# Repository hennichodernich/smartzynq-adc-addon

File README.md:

# smartzynq-adc-addon
KiCad files for the SmartZynq ADC addon board

*Make sure to reconfigure VCCIO on the SmartZynq to 2.5V!*

Licensed under CERN-OHL-W v2

## Hardware build

This board is supposed to be mounted on a HelloFPGA Smart Zynq SL FPGA board such as the one that can be purchased [here](https://aliexpress.com/item/1005006384235496.html).

It can be nicely mounted in an enclosure such as [this one](https://aliexpress.com/item/1005007125132369.html):

## Receive performance

The receive performance of the [sdr_receiver_ft8_122_88 project](https://github.com/hennichodernich/hellofpga-smartzynq-notes/tree/main/projects/sdr_receiver_ft8_122_88) is really good (on 22m EFHW):

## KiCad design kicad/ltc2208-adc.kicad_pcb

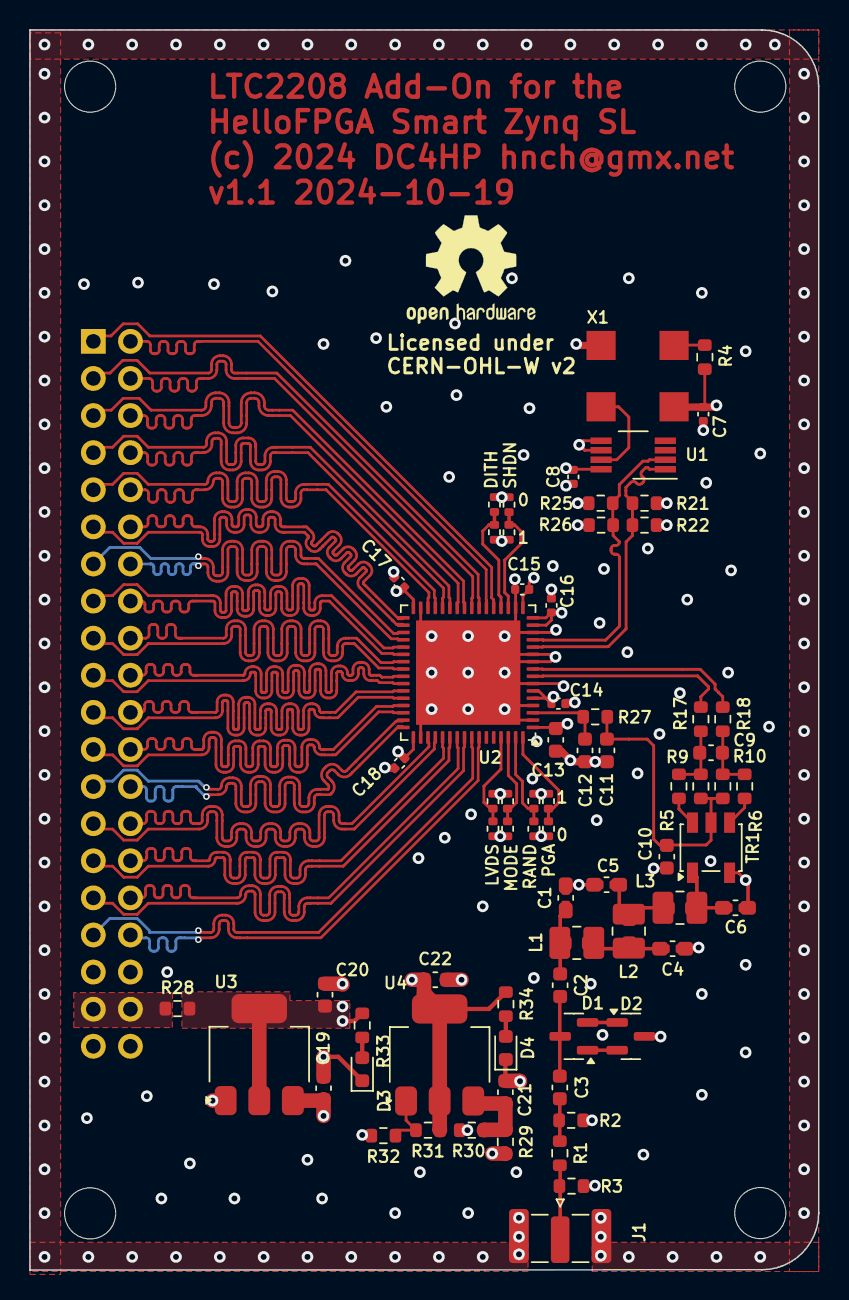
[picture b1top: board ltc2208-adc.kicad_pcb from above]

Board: 4 copper layers, 54.0 x 84.9 mm, 75 parts (1 on the bottom side), 70 nets.

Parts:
C1, C4, C5, C6: C; C_0603_0402_HandSolder_Combo
C2, C3: 1u; C_0603_1608Metric
C7, C8, C14, C15, C16, C17, C18: 100n; C_0402_1005Metric
C9: 4.7p; C_0603_1608Metric
C10, C11: 10n; C_0603_1608Metric
C12, C13, C19, C20, C21, C22: 2.2u; C_0603_1608Metric
D1, D2: BAV99; SOT-23
D3, D4: LED; LED_0603_1608Metric
H1, H2, H3, H4: MountingHole; MountingHole_3.5mm
J1: Conn_Coaxial; SMA_Samtec_SMA-J-P-H-ST-EM1_EdgeMount
J2: Conn_02x20_Odd_Even; PinSocket_2x20_P2.54mm_Vertical
L1, L2, L3: L; L_1008_0805_0603_HandSolder_Combo
R1: 5.1; R_0603_1608Metric
R2, R3: 1k; R_0603_1608Metric
R4: 4.7k; R_0603_1608Metric
R5, R6, R17, R18: 10; R_0603_1608Metric
R7, R8, R11, R12, R13, R14, R15, R16, R19, R20, R23, R24: 4.7k; R_0402_1005Metric
R9, R10: 33.2; R_0603_1608Metric
R21, R25: 130; R_0603_1608Metric
R22, R26: 83; R_0603_1608Metric
R27: 100; R_0603_1608Metric
R28, R29, R30: 0; R_0603_1608Metric
R31, R32: R; R_0603_1608Metric
R33, R34: 470; R_0603_1608Metric
TR1: ETC4-1-2; Transformer_MACOM_SM-22
U1: SN65EPT22; VSSOP-8_3.0x3.0mm_P0.65mm
U2: LTC2208; QFN-64-1EP_9x9mm_P0.5mm_EP7.15x7.15mm
U3: LT1117-3.3; SOT-223-3_TabPin2
U4: LT1117-ADJ; SOT-223-3_TabPin2
X1: XO91; Oscillator_SMD_EuroQuartz_XO91-4Pin_7.0x5.0mm

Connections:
+3.3V: C7.1, C8.1, C13.1, C14.1, C15.1, C16.1, C20.1, R4.1, R7.1, R11.1, R13.1, R15.1, R19.1, R21.1, R23.1, R25.1, R28.2, R33.1, U1.8 (VCC), U2.1 (SENSE), U2.5 (VDD), U2.6 (VDD), U2.15 (VDD), U2.16 (VDD), U2.17 (VDD), U3.2 (VO), X1.4 (V+)
/3V3_FPGA: J2.37, J2.38, R28.1, R30.1
/AIN2+: C9.1, R5.2, R9.1, R17.1
/AIN2-: C9.2, R6.2, R10.2, R18.1
/AIN+: R17.2, U2.8 (AIN+)
/AIN-: R18.2, U2.9 (AIN-)
/CLK_N: J2.18, U2.39 (OFB)
/CLK_P: J2.17, U2.40 (CLKOUTB)
/D0_N: J2.1, U2.21 (DB0)
/D0_P: J2.2, U2.22 (DB1)
/D1_N: J2.3, U2.23 (DB2)
/D1_P: J2.4, U2.24 (DB3)
/D2_N: J2.5, U2.25 (DB4)
/D2_P: J2.6, U2.26 (DB5)
/D3_N: J2.7, U2.27 (DB6)
/D3_P: J2.8, U2.28 (DB7)
/D4_N: J2.9, U2.29 (DB8)
/D4_P: J2.10, U2.30 (DB9)
/D5_N: J2.12, U2.33 (DB10)
/D5_P: J2.11, U2.34 (DB11)
/D6_N: J2.13, U2.35 (DB12)
/D6_P: J2.14, U2.36 (DB13)
/D7_N: J2.15, U2.37 (DB14)
/D7_P: J2.16, U2.38 (DB15)
/D8_N: J2.20, U2.41 (CLKOUTA)
/D8_P: J2.19, U2.42 (DA0)
/D9_N: J2.22, U2.43 (DA1)
/D9_P: J2.21, U2.44 (DA2)
/D10_N: J2.24, U2.45 (DA3)
/D10_P: J2.23, U2.46 (DA4)
/D11_N: J2.25, U2.47 (DA5)
/D11_P: J2.26, U2.48 (DA6)
/D12_N: J2.28, U2.51 (DA7)
/D12_P: J2.27, U2.52 (DA8)
/D13_N: J2.30, U2.53 (DA9)
/D13_P: J2.29, U2.54 (DA10)
/D14_N: J2.32, U2.55 (DA11)
/D14_P: J2.31, U2.56 (DA12)
/D15_N: J2.33, U2.57 (DA13)
/D15_P: J2.34, U2.58 (DA14)
/ENC+: R21.2, R22.1, U1.1 (DO+1), U2.12 (ENC+)
/ENC-: R25.2, R26.1, U1.2 (DO-1), U2.13 (ENC-)
/VBUS: C19.1, J2.39, J2.40, R29.1, U3.3 (VI)
GND: C1.2, C4.2, C5.2, C6.2, C7.2, C8.2, C10.2, C11.2, C12.2, C13.2, C14.2, C15.2, C16.2, C17.2, C18.2, C19.2, C20.2, C21.2, C22.2, D2.3 (K), D3.1 (K), D4.1 (K), J1.2 (Ext), J2.35, J2.36, R2.2, R3.2, R8.2, R12.2, R14.2, R16.2, R20.2, R22.2, R24.2, R26.2, R32.2, TR1.2, U1.5 (GND), U1.6 (DI2), U2.2 (GND), U2.4 (GND), U2.7 (GND), U2.10 (GND), U2.11 (GND), U2.14 (GND), U2.18 (GND), U2.31 (OGND), U2.50 (OGND), U2.65 (GND), U3.1 (GND), X1.2 (GND)
unnamed: C1.1, C2.1, L1.1
unnamed: C2.2, C3.1, D1.3 (K)
unnamed: C3.2, R1.1, R2.1
unnamed: C4.1, L1.2, L2.1
unnamed: C5.1, L2.2, L3.1
unnamed: C6.1, L3.2, TR1.1
unnamed: C10.1, C11.1, R9.2, R10.1, R27.1, TR1.4
unnamed: D1.2 (A), D2.1 (K)
unnamed: D1.1 (K), D2.2 (A)
unnamed: D3.2 (A), R33.2
unnamed: D4.2 (A), R34.2
unnamed: J1.1 (In), R1.2, R3.1
unnamed: R5.1, TR1.5
unnamed: R6.1, TR1.3
unnamed: U1.7 (DI1), X1.3 (OUT)
unnamed: R19.2, R20.1, U2.20 (DITH)
unnamed: R13.2, R14.1, U2.61 (LVDS)
unnamed: R23.2, R24.1, U2.62 (MODE)
unnamed: R7.2, R8.1, U2.64 (PGA)
unnamed: R11.2, R12.1, U2.63 (RAND)
unnamed: R15.2, R16.1, U2.19 (SHDN)
unnamed: C12.1, R27.2, U2.3 (VCM)
unnamed: R31.2, R32.1, U4.1 (ADJ)
unnamed: C21.1, R29.2, R30.2, U4.3 (VI)
unnamed: R4.2, X1.1 (EN)
VDD: C17.1, C18.1, C22.1, R31.1, R34.1, U2.32 (OVDD), U2.49 (OVDD), U4.2 (VO)

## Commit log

2024-10-19 Clarified VCCIO issue
2024-10-21 Moved files into kicad subdir
2024-10-21 Added photos
2025-06-08 Added schematic as PDF

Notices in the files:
kicad/ltc2208-adc.kicad_pcb:
(c) 2024 DC4HP hnch@gmx.net
